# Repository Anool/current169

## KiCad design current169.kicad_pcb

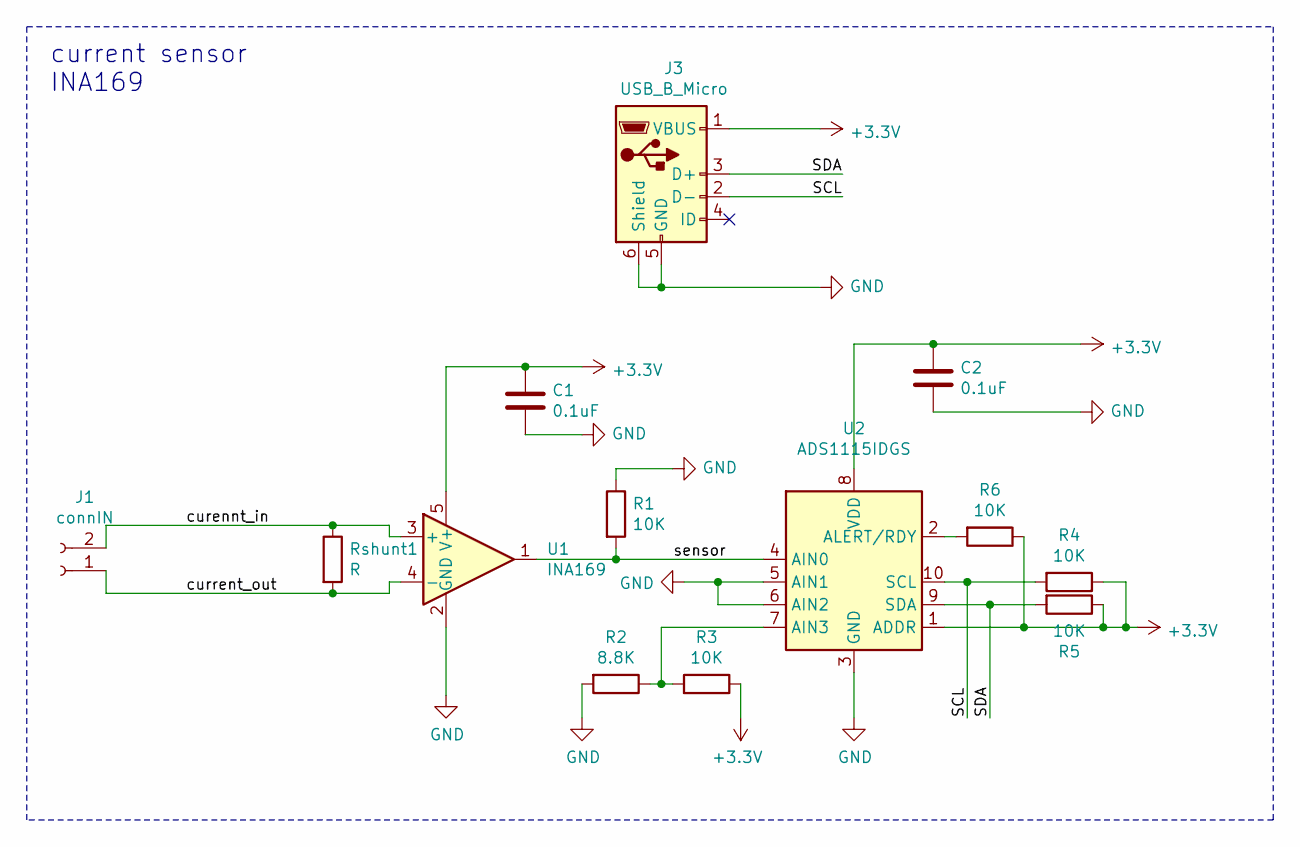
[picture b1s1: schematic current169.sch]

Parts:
C1, C2: 0.1uF; C_1210_3225Metric
J1: connIN; TerminalBlock_bornier-2_P5.08mm
J3: USB_B_Micro; USB_Micro-B_GCT_USB3076-30-A
R1, R3, R4, R5, R6: 10K; R_0402_1005Metric
R2: 8.8K; R_0402_1005Metric
Rshunt1: R; R_2512_6332Metric
U1: INA169; SOT-23-5
U2: ADS1115IDGS; TSSOP-10_3x3mm_P0.5mm

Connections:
+3V3: C1.1, C2.1, J3.1 (VBUS), R3.1, R4.1, R5.1, R6.1, U1.5 (V+), U2.1 (ADDR), U2.8 (VDD)
/SCL: J3.2 (D-), R4.2, U2.10 (SCL)
/SDA: J3.3 (D+), R5.2, U2.9 (SDA)
/curennt_in: J1.2, Rshunt1.1, U1.3 (+)
/current_out: J1.1, Rshunt1.2, U1.4 (-)
/sensor: R1.2, U1.1, U2.4 (AIN0)
GND: C1.2, C2.2, J3.5 (GND), J3.6 (Shield), R1.1, R2.2, U1.2 (GND), U2.3 (GND), U2.5 (AIN1), U2.6 (AIN2)
unnamed: R2.1, R3.2, U2.7 (AIN3)
unnamed: R6.2, U2.2 (ALERT/RDY)

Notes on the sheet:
current sensor INA169

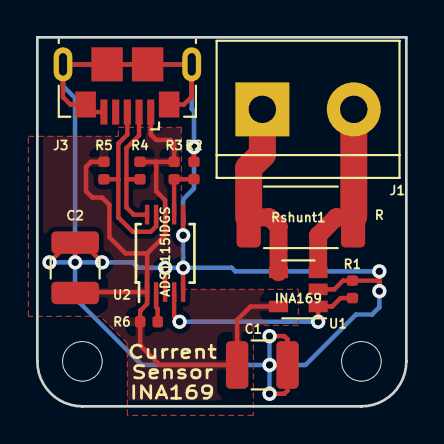
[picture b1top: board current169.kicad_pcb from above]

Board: 2 copper layers, 20.5 x 20.5 mm, 13 parts (0 on the bottom side), 9 nets.

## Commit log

2018-12-09 current sensor breakout
